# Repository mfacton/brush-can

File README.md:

# brush-can
Dense triple brushed motor controller with CAN FD

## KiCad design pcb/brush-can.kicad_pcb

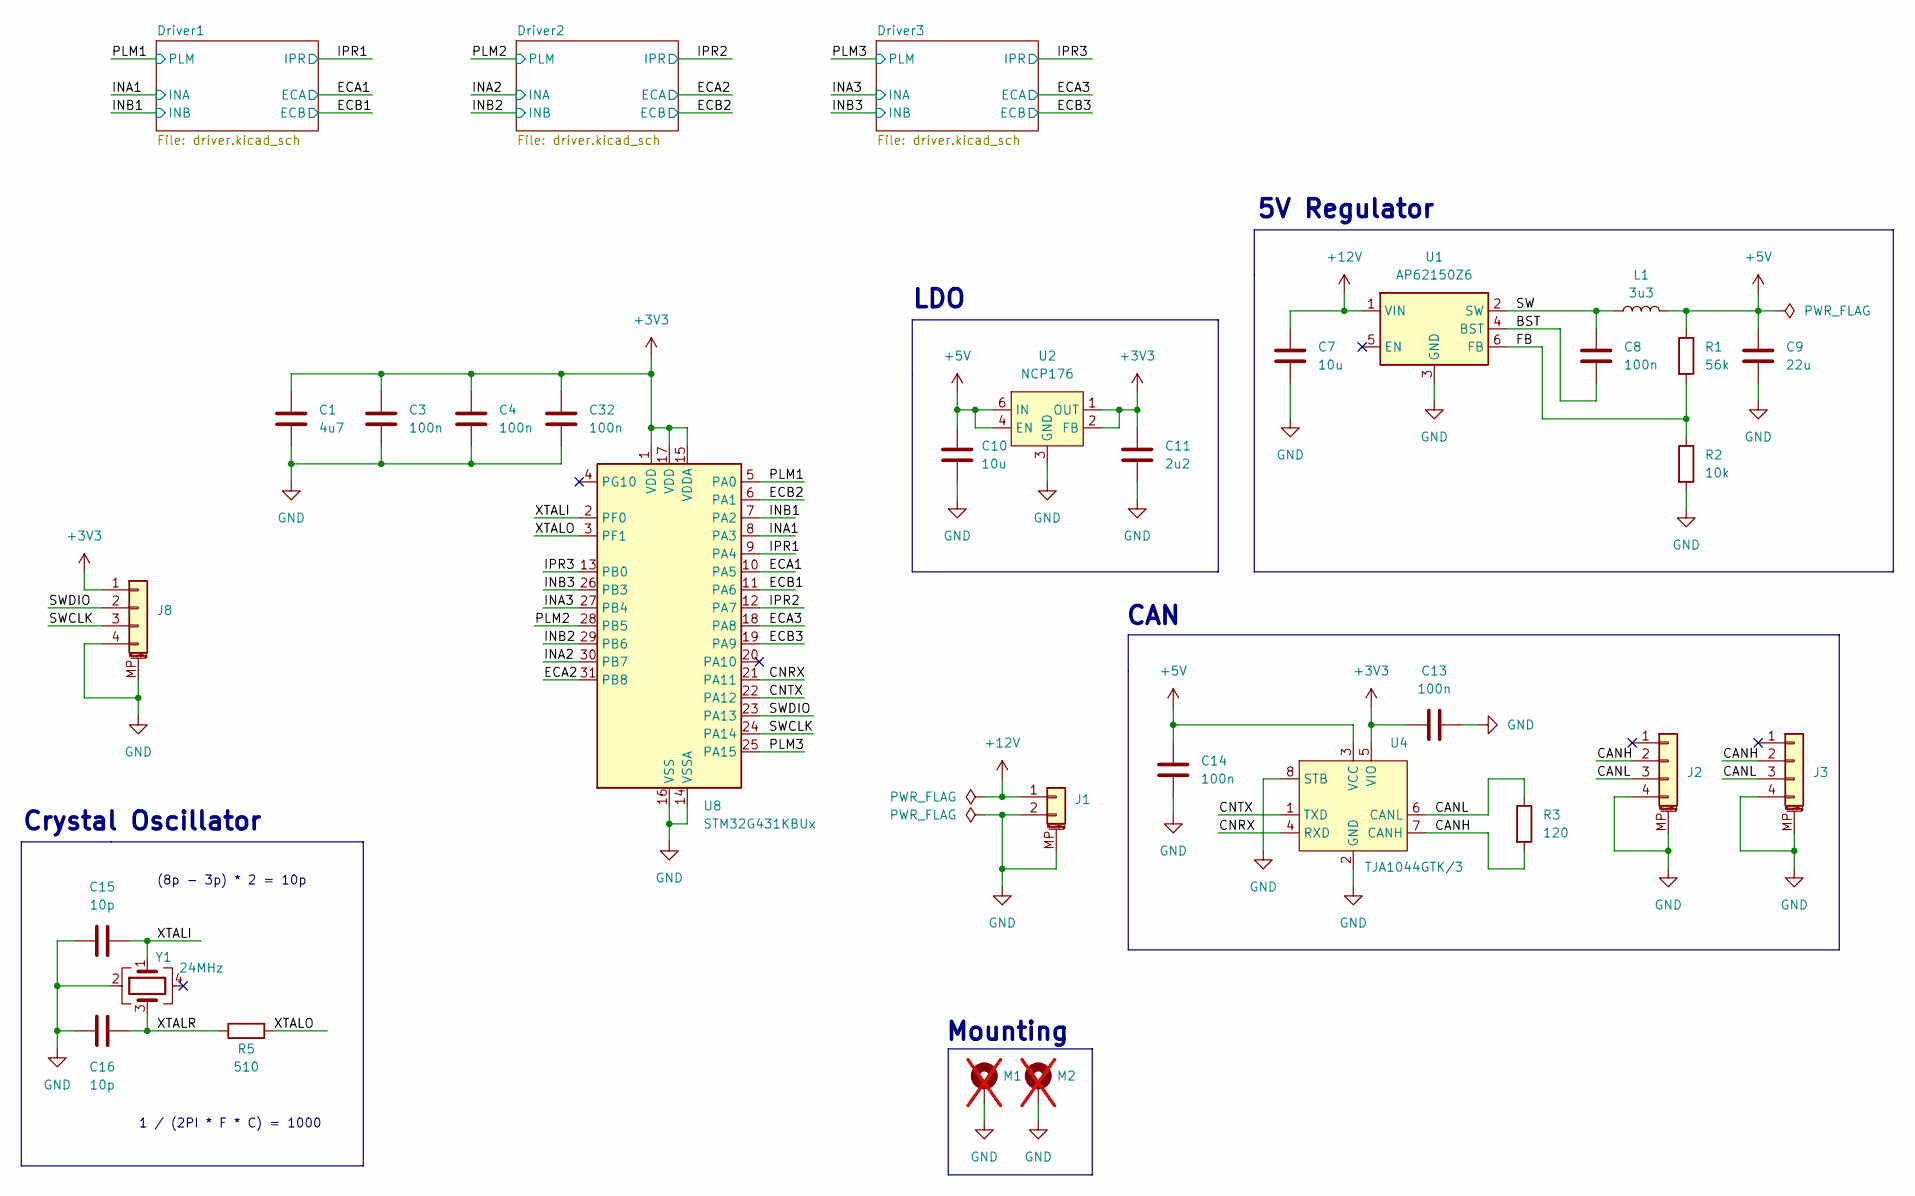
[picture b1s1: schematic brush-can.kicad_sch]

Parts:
C1: 4u7; C_0402_1005Metric; LCSC C23733
C3, C4, C8, C13, C14, C32: 100n; C_0402_1005Metric; LCSC C1525
C7: 10u; C_0603_1608Metric; LCSC C96446
C9: 22u; C_0805_2012Metric; LCSC C45783
C10: 10u; C_0603_1608Metric; LCSC C19702
C11: 2u2; C_0402_1005Metric; LCSC C12530
C15, C16: 10p; C_0402_1005Metric; LCSC C32949
J1: Conn_01x02_MountingPin; JST_GH_SM02B-GHS-TB_1x02-1MP_P1.25mm_Horizontal; LCSC C189893
J2, J3: Conn_01x04_MountingPin; JST_GH_SM04B-GHS-TB_1x04-1MP_P1.25mm_Horizontal; LCSC C189895
J8: Conn_01x04_MountingPin; JST_SH_BM04B-SRSS-TB_1x04-1MP_P1.00mm_Vertical; LCSC C160390
L1: 3u3; L_Chilisin_BMRA00040420; LCSC C207829
M1, M2: 24939; not fitted
R1: 56k; R_0402_1005Metric; LCSC C25796
R2: 10k; R_0402_1005Metric; LCSC C25744
R3: 120; R_1206_3216Metric_Pad1.30x1.75mm_HandSolder; LCSC C17909
R5: 510; R_0402_1005Metric; LCSC C25123
U1: AP62150Z6; SOT-563; LCSC C3193206
U2: NCP176; DFN-6-1EP_1.2x1.2mm_P0.4mm_EP0.3x0.94mm_PullBack; LCSC C233363
U4: TJA1044GTK/3; HVSON-8-1EP_3x3mm_P0.65mm_EP1.6x2.4mm; LCSC C2157795
U8: STM32G431KBUx; QFN-32-1EP_5x5mm_P0.5mm_EP3.45x3.45mm; LCSC C1341901
Y1: 24MHz; Crystal_SMD_1612-4P; LCSC C2929397

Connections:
+3V3: C1.1, C3.1, C4.1, C11.1, C13.1, C32.1, J8.1, U2.1 (OUT), U2.2 (FB), U4.5 (VIO), U8.1 (VDD), U8.15 (VDDA), U8.17 (VDD); also elsewhere on the board
+5V: C9.1, C10.1, C14.2, L1.2, R1.1, U2.4 (EN), U2.6 (IN), U4.3 (VCC)
+12V: C7.1, J1.1, U1.1 (VIN); also elsewhere on the board
/BST: C8.2, U1.4 (BST)
/CANH: J2.2, J3.2, R3.2, U4.7 (CANH)
/CANL: J2.3, J3.3, R3.1, U4.6 (CANL)
/CNRX: U4.4 (RXD), U8.21 (PA11)
/CNTX: U4.1 (TXD), U8.22 (PA12)
/ECA1: U8.10 (PA5); also elsewhere on the board
/ECA2: U8.31 (PB8); also elsewhere on the board
/ECA3: U8.18 (PA8); also elsewhere on the board
/ECB1: U8.11 (PA6); also elsewhere on the board
/ECB2: U8.6 (PA1); also elsewhere on the board
/ECB3: U8.19 (PA9); also elsewhere on the board
/FB: R1.2, R2.1, U1.6 (FB)
/INA1: U8.8 (PA3); also elsewhere on the board
/INA2: U8.30 (PB7); also elsewhere on the board
/INA3: U8.27 (PB4); also elsewhere on the board
/INB1: U8.7 (PA2); also elsewhere on the board
/INB2: U8.29 (PB6); also elsewhere on the board
/INB3: U8.26 (PB3); also elsewhere on the board
/IPR1: U8.9 (PA4); also elsewhere on the board
/IPR2: U8.12 (PA7); also elsewhere on the board
/IPR3: U8.13 (PB0); also elsewhere on the board
/PLM1: U8.5 (PA0); also elsewhere on the board
/PLM2: U8.28 (PB5); also elsewhere on the board
/PLM3: U8.25 (PA15); also elsewhere on the board
/SW: C8.1, L1.1, U1.2 (SW)
/SWCLK: J8.3, U8.24 (PA14)
/SWDIO: J8.2, U8.23 (PA13)
/XTALI: C15.2, U8.2 (PF0), Y1.1
/XTALO: R5.2, U8.3 (PF1)
/XTALR: C16.2, R5.1, Y1.3
GND: C1.2, C3.2, C4.2, C7.2, C9.2, C10.2, C11.2, C13.2, C14.1, C15.1, C16.1, C32.2, J1.2, J1.MP (MountPin), J2.4, J2.MP (MountPin), J3.4, J3.MP (MountPin), J8.4, J8.MP (MountPin), M1.MP, M2.MP, R2.2, U1.3 (GND), U2.3 (GND), U2.7 (EPAD), U4.2 (GND), U4.8 (STB), U4.9 (EPAD), U8.14 (VSSA), U8.16 (VSS), U8.32 (VSS), U8.33 (VSS), Y1.2; also elsewhere on the board

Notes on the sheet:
CAN
Mounting
5V Regulator
(8p - 3p) * 2 = 10p
LDO
Crystal Oscillator
1 / (2PI * F * C) = 1000

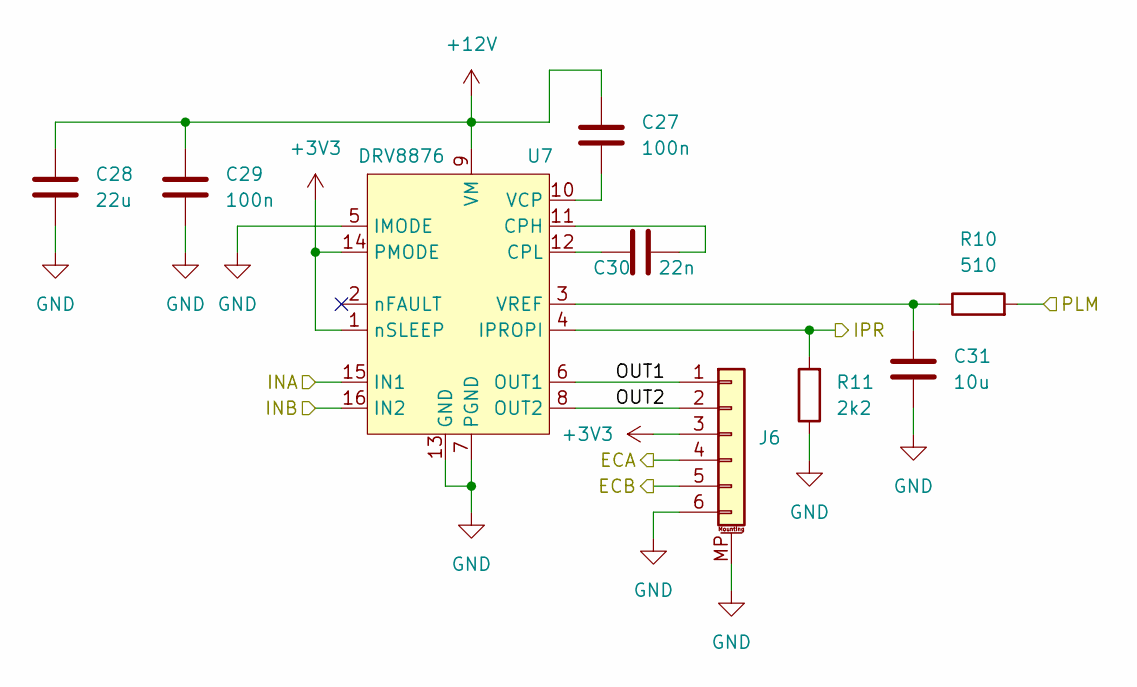
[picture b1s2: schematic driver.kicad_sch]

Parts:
C27, C29: 100n; C_0402_1005Metric; LCSC C307331
C28: 22u; C_1206_3216Metric; LCSC C12891
C30: 22n; C_0402_1005Metric; LCSC C1532
C31: 10u; C_0402_1005Metric; LCSC C15525
J6: Conn_01x06_MountingPin; JST_SH_SM06B-SRSS-TB_1x06-1MP_P1.00mm_Horizontal; LCSC C160405
R10: 510; R_0402_1005Metric; LCSC C25123
R11: 2k2; R_0402_1005Metric; LCSC C25879
U7: DRV8876; QFN-16-1EP_3x3mm_P0.5mm_EP1.7x1.7mm_ThermalVias; LCSC C1852100

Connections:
+3V3: J6.3, U7.1 (nSLEEP), U7.14 (PMODE); also elsewhere on the board
+12V: C27.1, C28.1, C29.1, U7.9 (VM); also elsewhere on the board
/Driver3/OUT1: J6.1, U7.6 (OUT1)
/Driver3/OUT2: J6.2, U7.8 (OUT2)
/ECA3: J6.4; also elsewhere on the board
/ECB3: J6.5; also elsewhere on the board
/INA3: U7.15 (IN1); also elsewhere on the board
/INB3: U7.16 (IN2); also elsewhere on the board
/IPR3: R11.2, U7.4 (IPROPI); also elsewhere on the board
/PLM3: R10.2; also elsewhere on the board
GND: C28.2, C29.2, C31.2, J6.6, J6.MP (MountPin), R11.1, U7.5 (IMODE), U7.7 (PGND), U7.13 (GND), U7.17 (PAD); also elsewhere on the board
unnamed: C30.1, U7.11 (CPH)
unnamed: C30.2, U7.12 (CPL)
unnamed: C27.2, U7.10 (VCP)
unnamed: C31.1, R10.1, U7.3 (VREF)

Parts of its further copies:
C17, C19, C22, C24: 100n; C_0402_1005Metric; LCSC C307331
C18, C23: 22u; C_1206_3216Metric; LCSC C12891
C20, C25: 22n; C_0402_1005Metric; LCSC C1532
C21, C26: 10u; C_0402_1005Metric; LCSC C15525
J4, J5: Conn_01x06_MountingPin; JST_SH_SM06B-SRSS-TB_1x06-1MP_P1.00mm_Horizontal; LCSC C160405
R6, R8: 510; R_0402_1005Metric; LCSC C25123
R7, R9: 2k2; R_0402_1005Metric; LCSC C25879
U5, U6: DRV8876; QFN-16-1EP_3x3mm_P0.5mm_EP1.7x1.7mm_ThermalVias; LCSC C1852100

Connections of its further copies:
+3V3: J4.3, J5.3, U5.1 (nSLEEP), U5.14 (PMODE), U6.1 (nSLEEP), U6.14 (PMODE); also elsewhere on the board
+12V: C17.1, C18.1, C19.1, C22.1, C23.1, C24.1, U5.9 (VM), U6.9 (VM); also elsewhere on the board
/Driver1/OUT1: J4.1, U5.6 (OUT1)
/Driver1/OUT2: J4.2, U5.8 (OUT2)
/Driver2/OUT1: J5.1, U6.6 (OUT1)
/Driver2/OUT2: J5.2, U6.8 (OUT2)
/ECA1: J4.4; also elsewhere on the board
/ECA2: J5.4; also elsewhere on the board
/ECB1: J4.5; also elsewhere on the board
/ECB2: J5.5; also elsewhere on the board
/INA1: U5.15 (IN1); also elsewhere on the board
/INA2: U6.15 (IN1); also elsewhere on the board
/INB1: U5.16 (IN2); also elsewhere on the board
/INB2: U6.16 (IN2); also elsewhere on the board
/IPR1: R7.2, U5.4 (IPROPI); also elsewhere on the board
/IPR2: R9.2, U6.4 (IPROPI); also elsewhere on the board
/PLM1: R6.2; also elsewhere on the board
/PLM2: R8.2; also elsewhere on the board
GND: C18.2, C19.2, C21.2, C23.2, C24.2, C26.2, J4.6, J4.MP (MountPin), J5.6, J5.MP (MountPin), R7.1, R9.1, U5.5 (IMODE), U5.7 (PGND), U5.13 (GND), U5.17 (PAD), U6.5 (IMODE), U6.7 (PGND), U6.13 (GND), U6.17 (PAD); also elsewhere on the board
unnamed: C20.1, U5.11 (CPH)
unnamed: C20.2, U5.12 (CPL)
unnamed: C17.2, U5.10 (VCP)
unnamed: C21.1, R6.1, U5.3 (VREF)
unnamed: C25.1, U6.11 (CPH)
unnamed: C25.2, U6.12 (CPL)
unnamed: C22.2, U6.10 (VCP)
unnamed: C26.1, R8.1, U6.3 (VREF)

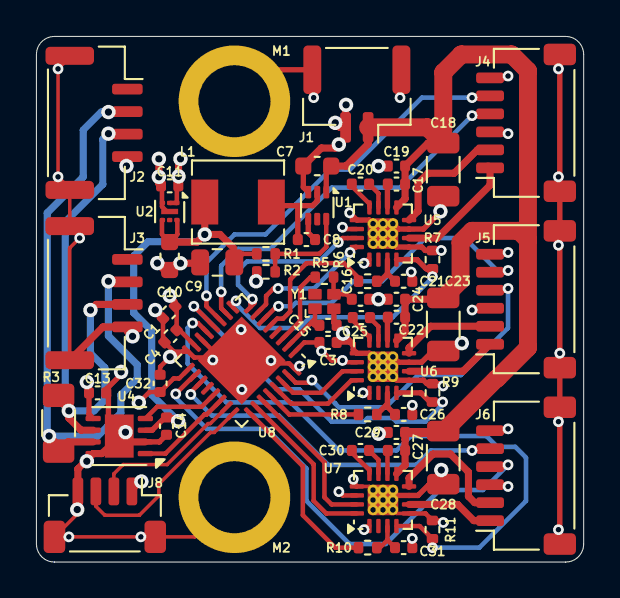
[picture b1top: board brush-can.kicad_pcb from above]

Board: 4 copper layers, 30.4 x 29.2 mm, 56 parts (0 on the bottom side), 52 nets.

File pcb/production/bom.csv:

Designator,Footprint,Quantity,Value,LCSC Part #
C1,0402,1,4u7,C23733
C10,0603,1,10u,C19702
C11,0402,1,2u2,C12530
"C13, C14, C3, C32, C4, C8",0402,6,100n,C1525
"C15, C16",0402,2,10p,C32949
"C17, C19, C22, C24, C27, C29",0402,6,100n,C307331
"C18, C23, C28",1206,3,22u,C12891
"C20, C25, C30",0402,3,22n,C1532
"C21, C26, C31",0402,3,10u,C15525
C7,0603,1,10u,C96446
C9,0805,1,22u,C45783
J1,JST_GH_SM02B-GHS-TB_1x02-1MP_P1.25mm_Horizontal,1,Conn_01x02_MountingPin,C189893
"J2, J3",JST_GH_SM04B-GHS-TB_1x04-1MP_P1.25mm_Horizontal,2,Conn_01x04_MountingPin,C189895
"J4, J5, J6",JST_SH_SM06B-SRSS-TB_1x06-1MP_P1.00mm_Horizontal,3,Conn_01x06_MountingPin,C160405
J8,JST_SH_BM04B-SRSS-TB_1x04-1MP_P1.00mm_Vertical,1,Conn_01x04_MountingPin,C160390
L1,L_Chilisin_BMRA00040420,1,3u3,C207829
R1,0402,1,56k,C25796
"R10, R5, R6, R8",0402,4,510,C25123
"R11, R7, R9",0402,3,2k2,C25879
R2,0402,1,10k,C25744
R3,1206,1,120,C17909
U1,SOT-563,1,AP62150Z6,C3193206
U2,DFN-6-1EP_1.2x1.2mm_P0.4mm_EP0.3x0.94mm_PullBack,1,NCP176,C233363
U4,HVSON-8-1EP_3x3mm_P0.65mm_EP1.6x2.4mm,1,TJA1044GTK/3,C2157795
"U5, U6, U7",QFN-16-1EP_3x3mm_P0.5mm_EP1.7x1.7mm_ThermalVias,3,DRV8876,C1852100
U8,QFN-32-1EP_5x5mm_P0.5mm_EP3.45x3.45mm,1,STM32G431KBUx,C1341901
Y1,Crystal_SMD_1612-4P,1,24MHz,C2929397

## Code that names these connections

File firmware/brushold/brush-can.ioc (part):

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Mcu.Name=STM32G431K(6-8-B)Ux
Mcu.Package=UFQFPN32
Mcu.UserName=STM32G431KBUx
PA0.Signal=S_TIM2_CH1
PA1.GPIOParameters=GPIO_Label
PA1.GPIO_Label=ECB2
PA1.Signal=GPIO_Input
PA11.Mode=FDCAN_Activate
PA11.Signal=FDCAN1_RX
PA12.Mode=FDCAN_Activate
PA12.Signal=FDCAN1_TX
PA13.Mode=Serial_Wire
PA13.Signal=SYS_JTMS-SWDIO
PA14.Mode=Serial_Wire
PA14.Signal=SYS_JTCK-SWCLK
PA15.Signal=S_TIM8_CH1
PA2.Signal=S_TIM2_CH3
PA3.Signal=S_TIM2_CH4
PA4.Mode=IN17-Single-Ended
PA4.Signal=ADC2_IN17
PA5.GPIOParameters=GPIO_Label
PA5.GPIO_Label=ECA1
PA5.Signal=GPIO_Input
PA6.GPIOParameters=GPIO_Label
PA6.GPIO_Label=ECB1
PA6.Signal=GPIO_Input
PA7.Mode=IN4-Single-Ended
PA7.Signal=ADC2_IN4
PA8.GPIOParameters=GPIO_Label
PA8.GPIO_Label=ECA3
PA8.Signal=GPIO_Input
PA9.GPIOParameters=GPIO_Label
PA9.GPIO_Label=ECB3
PA9.Signal=GPIO_Input
PB0.Mode=IN15-Single-Ended
PB0.Signal=ADC1_IN15
PB3.Signal=S_TIM2_CH2
PB4.Signal=S_TIM3_CH1
PB5.Signal=S_TIM3_CH2
PB6.Signal=S_TIM4_CH1
PB7.Signal=S_TIM4_CH2
PB8-BOOT0.GPIOParameters=GPIO_Label
PB8-BOOT0.GPIO_Label=ECA2
PB8-BOOT0.Signal=GPIO_Input
PF0-OSC_IN.Mode=HSE-External-Oscillator
PF0-OSC_IN.Signal=RCC_OSC_IN
PF1-OSC_OUT.Mode=HSE-External-Oscillator
PF1-OSC_OUT.Signal=RCC_OSC_OUT
RCC.HSE_VALUE=24000000
RCC.SYSCLKFreq_VALUE=144000000
RCC.SYSCLKSource=RCC_SYSCLKSOURCE_PLLCLK
board=custom

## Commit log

2024-06-05 Finish schematic
2024-06-05 Initial configure pins
2024-06-05 Random save
2024-06-05 Rough layout of pcb
2024-06-05 Regenerate code
2024-06-06 Add inserts and change CAN connection
2024-06-06 Remove garbage
2024-06-07 Finish layout
2024-06-08 Wire most power
2024-06-10 Finish routing and rule checking
2024-06-10 Create production files
2024-06-10 Finish final details
2024-06-10 Finish pin setup
2024-06-10 Save
2024-06-12 Final production
2024-06-12 Edit lcsc part number
2024-07-11 Add improvements
2024-07-11 Change filename
2024-07-11 Add notes
2024-07-17 Remove old project
2024-07-17 Add fixes
2024-07-17 Set up can communication
2024-07-17 Setup set and get commands
2024-07-19 Finish implementing PID
2024-08-17 Make revision 2
2024-08-17 Save firmware from version 1
2024-10-04 Setup new firmware project
2024-10-07 Set up cmake interface to stm-lib
2024-10-10 Basic controller working
2024-10-10 Finish interface
2024-10-10 Change address
2024-10-11 Add direction change function and zero position
2024-11-01 Add position response on target set
